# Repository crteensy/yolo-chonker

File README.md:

# yolo-chonker

## if you are a betaflight dev and received an assembled board from crteensy

There is a branch with the "as-built" state that you received: https://github.com/crteensy/yolo-chonker/tree/as-built-20230303

It includes a description of minor mistakes and errors, and what paste (high temp, low temp) was used where.

## What this is

betaflight developer FC for the H735

The layout has 6 layers, and the decoupling is designed for oshpark's 6-layer stackup (see oshpark_6L_stackup.png)

- Format: 30x30 hole distance
- Battery voltage range: 2-6S
- 5V DCDC: LMR33620CRNXT
- 3V3: TPS62824
- Separate DCDC for HD out; LMR33620CRNXT set for 10V or 5V, configured with a solder jumper
- MCU: STM32H735
- peripherals that can be connected to the MCU with solder jumpers:
  - IMU: ICM-20602 and BMI270; dual gyro is possible
  - Flash: S25FL064L
  - Baro: DPS310
  - LEDs:
    - voltage rails LEDs: HD DCDC (5/10 V), 5V, 3V3
    - two standard LEDs for the FC
    - WS2812B including an output pad to attach more
  - battery voltage sensing
- SWD pads
- no analog OSD
- no HD connector

CC-BY-SA-4.0
https://creativecommons.org/licenses/by-sa/4.0/legalcode

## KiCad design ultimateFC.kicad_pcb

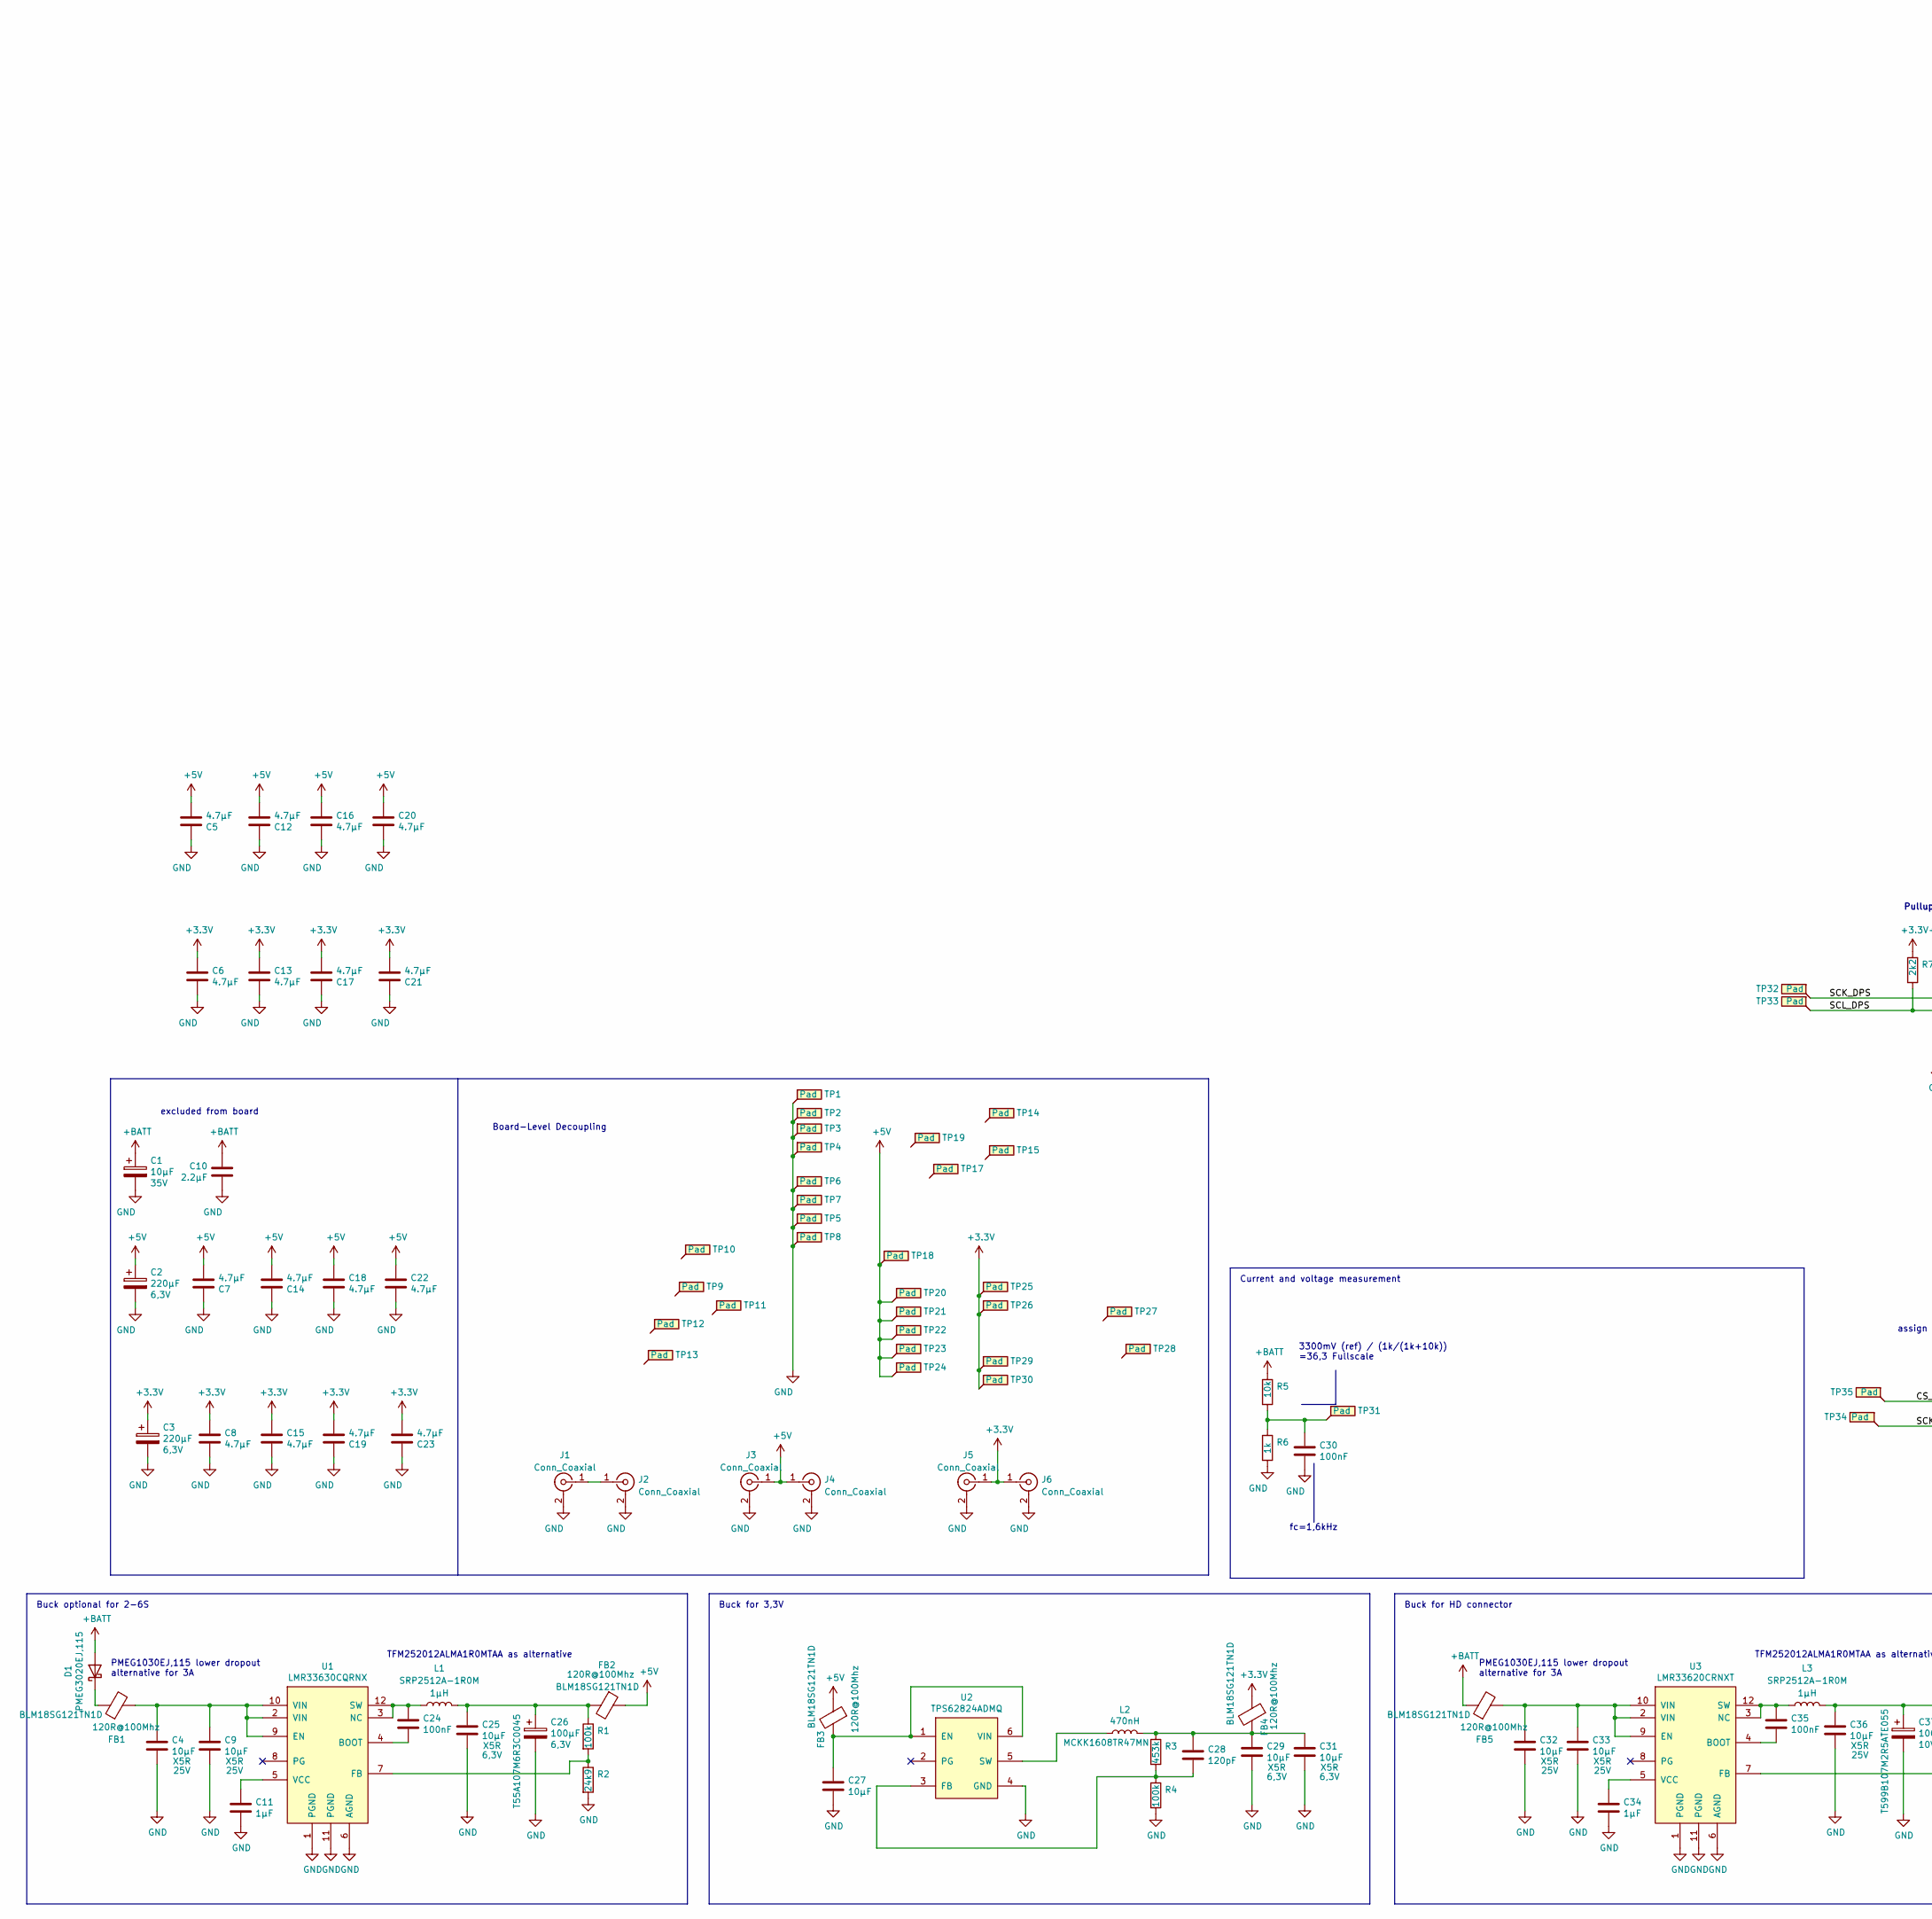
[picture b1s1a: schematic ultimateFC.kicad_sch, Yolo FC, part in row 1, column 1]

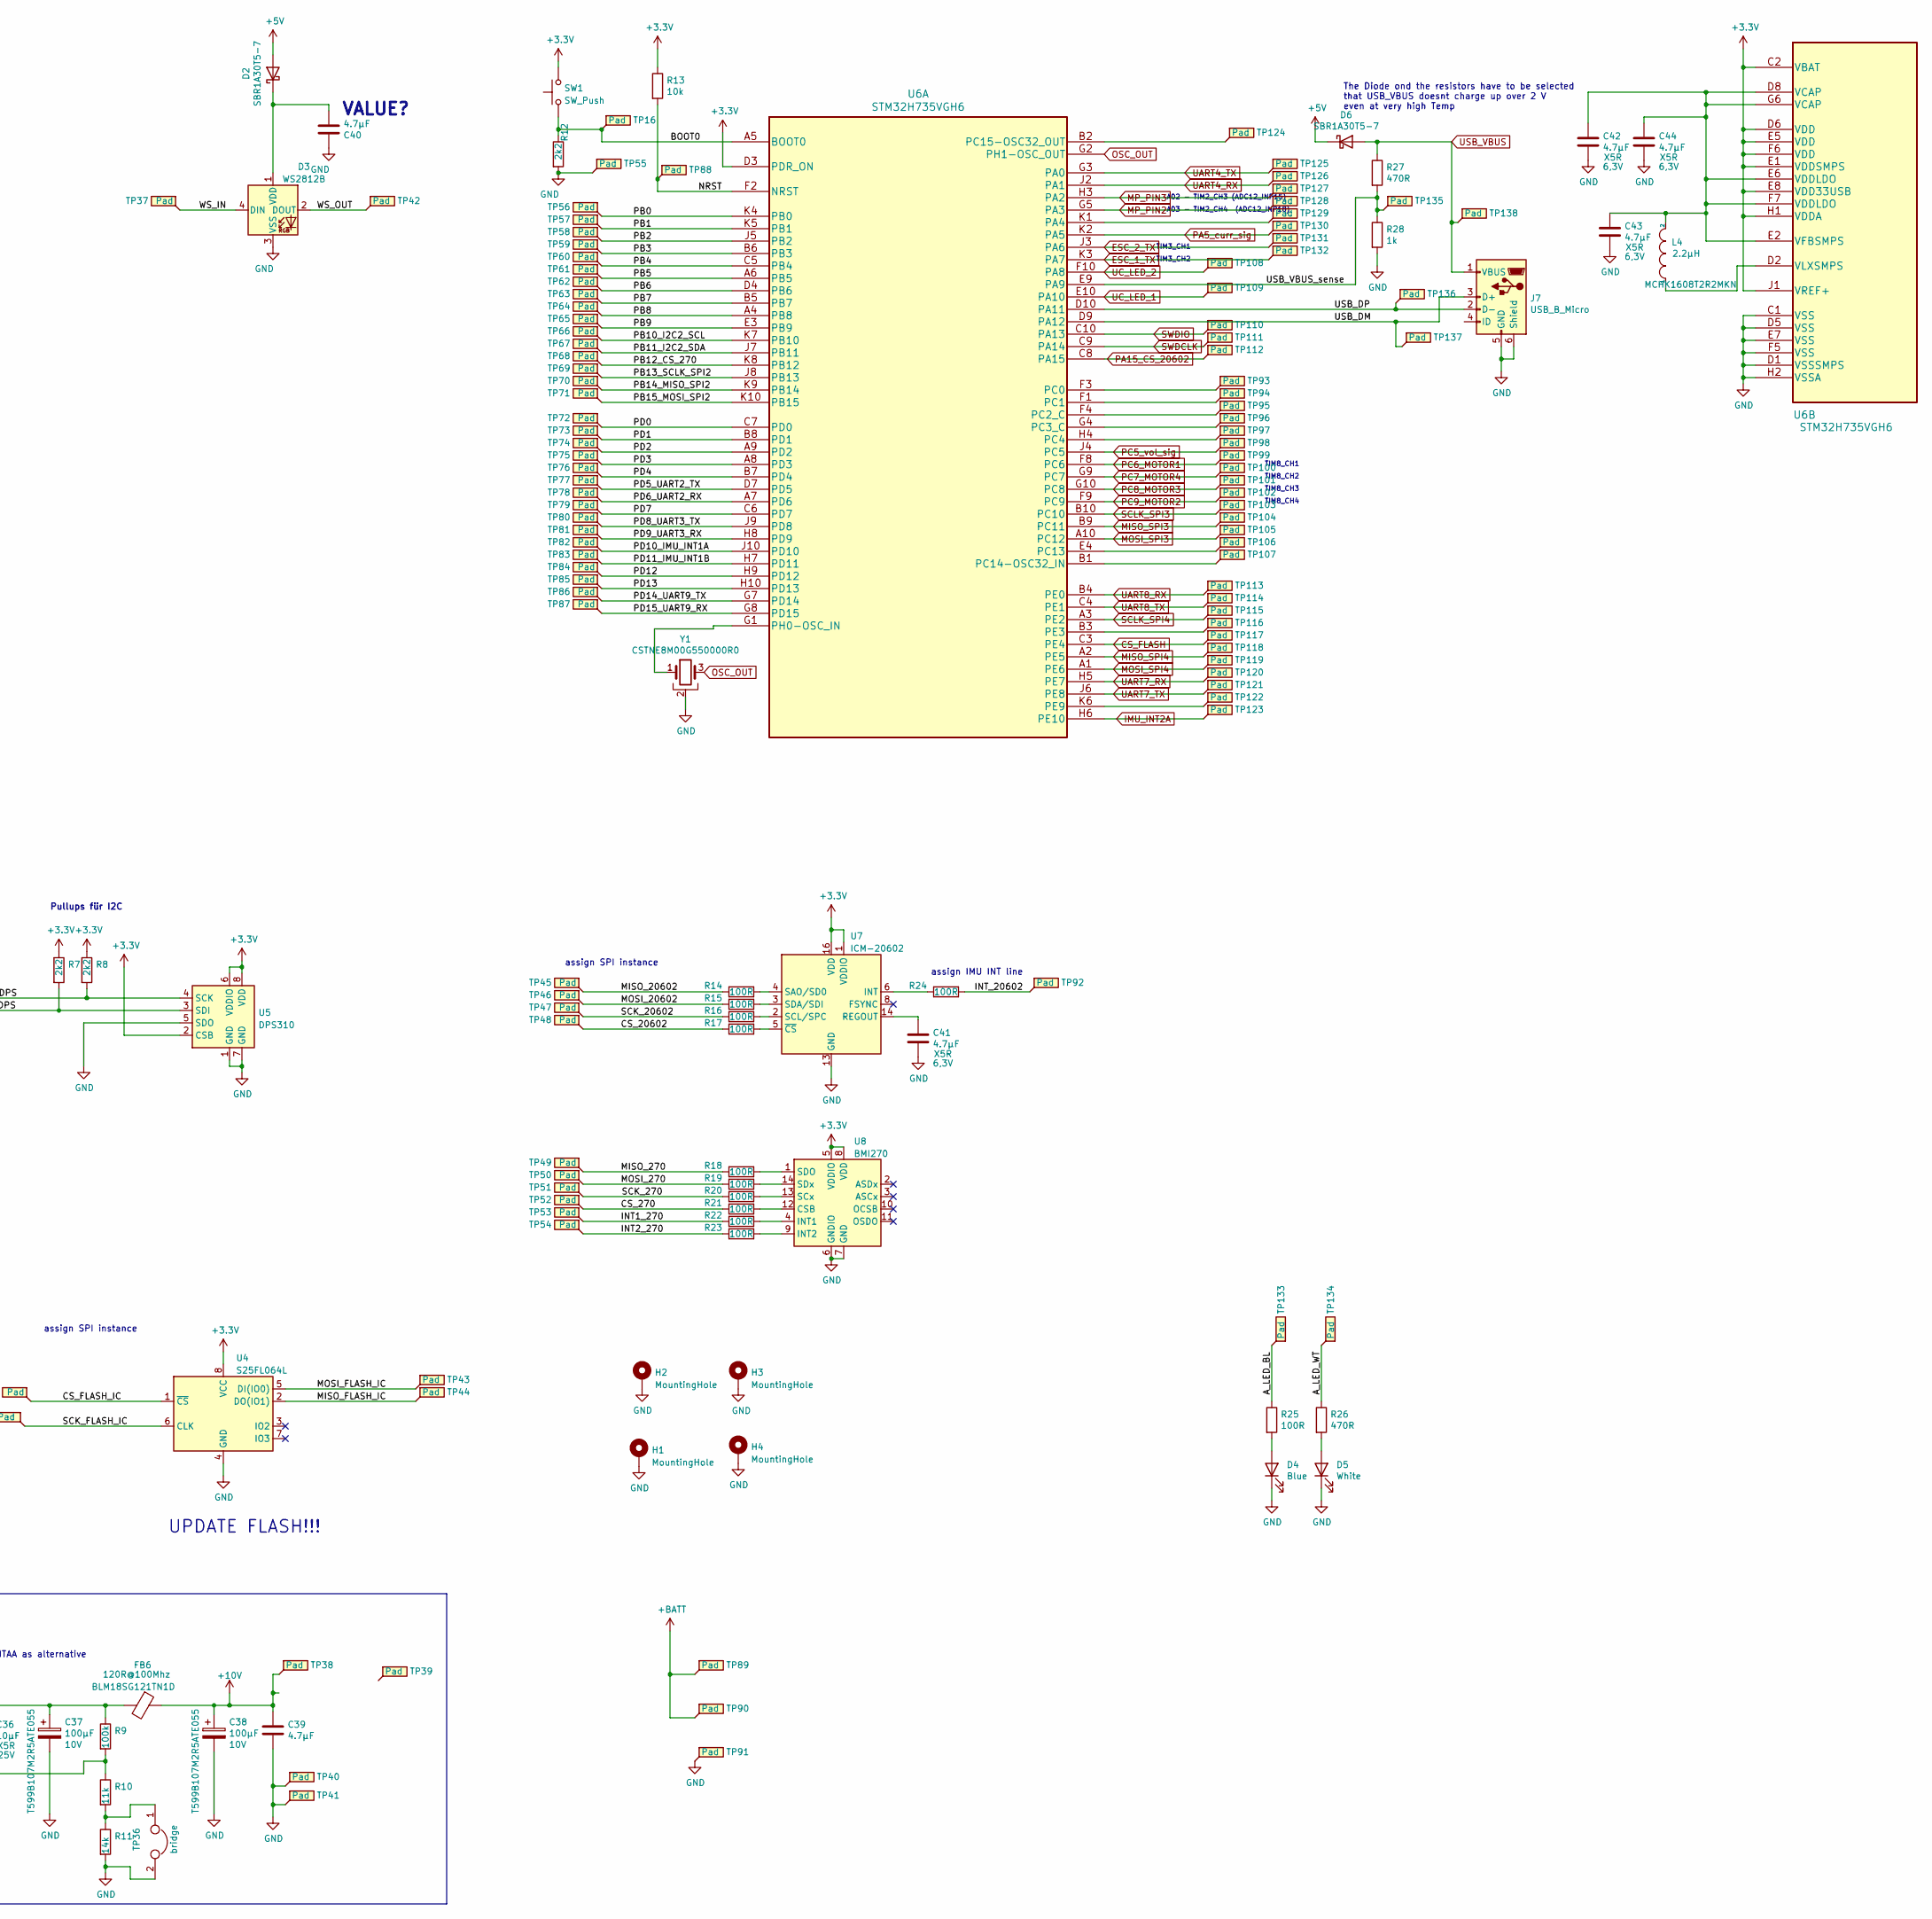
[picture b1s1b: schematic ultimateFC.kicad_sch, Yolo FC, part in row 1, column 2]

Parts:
C1: 10µF; CP_EIA-3216-18_Kemet-A
C2, C3: 220µF; CP_EIA-3528-15_AVX-H
C4, C9, C32, C33, C36: 10µF; C_1206_3216Metric
C5, C6, C7, C8, C12, C13, C14, C15, C16, C17, C18, C19, C20, C21, C22, C23, C39, C41, C42, C43, C44: 4.7µF; C_0402_1005Metric
C10: 2.2µF; C_0603_1608Metric
C11, C34: 1µF; C_0402_1005Metric
C24, C30, C35: 100nF; C_0402_1005Metric
C25, C27, C29, C31: 10µF; C_0603_1608Metric
C26: 100µF; CP_EIA-3216-10_Kemet-I
C28: 120pF; C_0402_1005Metric
C37, C38: 100µF; CP_EIA-3528-12_Kemet-T
C40: 4.7µF; C_0603_1608Metric
D1: PMEG3020EJ,115; D_SOD-323
D2, D6: SBR1A30T5-7; D_SOD-523
D3: WS2812B; LED_WS2812B_PLCC4_5.0x5.0mm_P3.2mm
D4: Blue; LED_0402_1005Metric
D5: White; LED_0402_1005Metric
FB1, FB2, FB3, FB4, FB5, FB6: 120R@100Mhz; L_0603_1608Metric
H1, H2, H3, H4: MountingHole; MountingHole_3.2mm_M3_DIN965_Pad
J1, J2, J3, J4, J5, J6: Conn_Coaxial; Amphenol_RF_A-4JA
J7: USB_B_Micro; USB_Micro-B_Amphenol_10118194_Horizontal
L1, L3: 1µH; L_Wuerth_MAPI-2506
L2: 470nH; L_0603_1608Metric
L4: 2.2µH; L_0603_1608Metric
R1, R4, R9: 100k; R_0402_1005Metric
R2: 24k9; R_0402_1005Metric
R3: 453k; R_0402_1005Metric
R5, R13: 10k; R_0402_1005Metric
R6, R28: 1k; R_0402_1005Metric
R7, R8, R12: 2k2; R_0402_1005Metric
R10: 11k; R_0402_1005Metric
R11: 14k; R_0402_1005Metric
R14, R15, R16, R17, R18, R19, R20, R21, R22, R23, R24, R25: 100R; R_0402_1005Metric
R26, R27: 470R; R_0402_1005Metric
SW1: SW_Push; SW_Push_1P1T-SH_NO_CK_KMR2xxG
TP1, TP3, TP4, TP6, TP7, TP18, TP21, TP22, TP23, TP24, TP29, TP30, TP38, TP40, TP41: Pad; chonker_pwr_pad
TP2, TP5, TP8, TP9, TP10, TP11, TP12, TP13, TP14, TP15, TP16, TP17, TP19, TP20, TP26, TP27, TP28, TP39, TP42, TP56, TP57, TP58, TP59, TP60, TP61, TP62, TP63, TP64, TP65, TP66, TP67, TP68, TP69, TP70, TP71, TP72, TP73, TP74, TP75, TP76, TP77, TP78, TP79, TP80, TP81, TP82, TP83, TP84, TP85, TP86, TP87, TP89, TP93, TP94, TP95, TP96, TP97, TP98, TP99, TP100, TP101, TP102, TP103, TP104, TP105, TP106, TP107, TP108, TP109, TP112, TP113, TP114, TP115, TP116, TP117, TP118, TP119, TP120, TP121, TP122, TP123, TP124, TP125, TP126, TP127, TP128, TP129, TP130, TP131, TP132: Pad; chonker_TestPoint_Pad_1.5x2.0mm
TP25, TP55, TP88, TP110, TP111: Pad; chonker_swd_pad
TP31, TP32, TP33, TP34, TP35, TP37, TP43, TP44, TP45, TP46, TP47, TP48, TP49, TP50, TP51, TP52, TP53, TP54, TP92, TP133, TP134, TP135, TP136, TP137, TP138: Pad; chonker_TestPoint_Pad_1.5x1.5mm
TP36: bridge; solderbridge_tiny
TP90, TP91: Pad; TestPoint_Pad_3.0x3.0mm
U1: LMR33630CQRNX; Texas_RNX0012B
U2: TPS62824ADMQ; VSON_HR6
U3: LMR33620CRNXT; Texas_RNX0012B
U4: S25FL064L; WSON-8_4x4mm_P0.8mm
U5: DPS310; Bosch_LGA-8_2x2.5mm_P0.65mm_ClockwisePinNumbering
U6: STM32H735VGH6; TFBGA-100_8x8mm_Layout10x10_P0.8mm
U7: ICM-20602; LGA-16_3x3mm_P0.5mm_LayoutBorder3x5y
U8: BMI270; Bosch_LGA-14_3x2.5mm_P0.5mm
Y1: CSTNE8M00G550000R0; Resonator_SMD_muRata_CSTxExxV-3Pin_3.0x1.1mm

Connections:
+3V3: C3.1, C6.1, C8.1, C13.1, C15.1, C17.2, C19.2, C21.2, C23.2, FB4.1, J5.1 (In), J6.1 (In), R7.1, R8.1, R13.1, SW1.2, TP25.1, TP26.1, TP29.1, TP30.1, U4.8 (VCC), U5.2 (CSB), U5.6 (VDDIO), U5.8 (VDD), U6.C2 (VBAT), U6.D3 (PDR_ON), U6.D6 (VDD), U6.E1 (VDDSMPS), U6.E5 (VDD), U6.E8 (VDD33USB), U6.F6 (VDD), U6.H1 (VDDA), U6.J1 (VREF+), U7.1 (VDDIO), U7.16 (VDD), U8.5 (VDDIO), U8.8 (VDD)
+5V: C2.1, C5.2, C7.2, C12.2, C14.2, C16.1, C18.1, C20.1, C22.1, D2.2 (A), D6.1 (K), FB2.1, FB3.1, J3.1 (In), J4.1 (In), TP18.1, TP20.1, TP21.1, TP22.1, TP23.1, TP24.1
+10V: C38.1, C39.1, FB6.1, TP38.1
+BATT: C1.1, C10.1, D1.2 (A), FB5.1, R5.1, TP89.1, TP90.1
/A_LED_BL: R25.1, TP133.1
/A_LED_WT: R26.1, TP134.1
/BOOT0: R12.1, SW1.1, TP16.1, U6.A5 (BOOT0)
/CS_270: R21.1, TP52.1
/CS_20602: R17.1, TP48.1
/CS_FLASH_IC: TP35.1, U4.1 (~CS)
/INT1_270: R22.1, TP53.1
/INT2_270: R23.1, TP54.1
/INT_20602: R24.2, TP92.1
/MISO_270: R18.1, TP49.1
/MISO_20602: R14.1, TP45.1
/MISO_FLASH_IC: TP44.1, U4.2 (DO(IO1))
/MOSI_270: R19.1, TP50.1
/MOSI_20602: R15.1, TP46.1
/MOSI_FLASH_IC: TP43.1, U4.5 (DI(IO0))
/NRST: R13.2, TP88.1, U6.F2 (NRST)
/PB0: TP56.1, U6.K4 (PB0)
/PB1: TP57.1, U6.K5 (PB1)
/PB2: TP58.1, U6.J5 (PB2)
/PB3: TP59.1, U6.B6 (PB3)
/PB4: TP60.1, U6.C5 (PB4)
/PB5: TP61.1, U6.A6 (PB5)
/PB6: TP62.1, U6.D4 (PB6)
/PB7: TP63.1, U6.B5 (PB7)
/PB8: TP64.1, U6.A4 (PB8)
/PB9: TP65.1, U6.E3 (PB9)
/PB10_I2C2_SCL: TP66.1, U6.K7 (PB10)
/PB11_I2C2_SDA: TP67.1, U6.J7 (PB11)
/PB12_CS_270: TP68.1, U6.K8 (PB12)
/PB13_SCLK_SPI2: TP69.1, U6.J8 (PB13)
/PB14_MISO_SPI2: TP70.1, U6.K9 (PB14)
/PB15_MOSI_SPI2: TP71.1, U6.K10 (PB15)
/PD0: TP72.1, U6.C7 (PD0)
/PD1: TP73.1, U6.B8 (PD1)
/PD2: TP74.1, U6.A9 (PD2)
/PD3: TP75.1, U6.A8 (PD3)
/PD4: TP76.1, U6.B7 (PD4)
/PD5_UART2_TX: TP77.1, U6.D7 (PD5)
/PD6_UART2_RX: TP78.1, U6.A7 (PD6)
/PD7: TP79.1, U6.C6 (PD7)
/PD8_UART3_TX: TP80.1, U6.J9 (PD8)
/PD9_UART3_RX: TP81.1, U6.H8 (PD9)
/PD10_IMU_INT1A: TP82.1, U6.J10 (PD10)
/PD11_IMU_INT1B: TP83.1, U6.H7 (PD11)
/PD12: TP84.1, U6.H9 (PD12)
/PD13: TP85.1, U6.H10 (PD13)
/PD14_UART9_TX: TP86.1, U6.G7 (PD14)
/PD15_UART9_RX: TP87.1, U6.G8 (PD15)
/SCK_270: R20.1, TP51.1
/SCK_20602: R16.1, TP47.1
/SCK_DPS: R8.2, TP32.1, U5.4 (SCK)
/SCK_FLASH_IC: TP34.1, U4.6 (CLK)
/SCL_DPS: R7.2, TP33.1, U5.3 (SDI)
/USB_DM: J7.3 (D+), TP137.1, U6.D9 (PA12)
/USB_DP: J7.2 (D-), TP136.1, U6.D10 (PA11)
/USB_VBUS_sense: R27.2, R28.1, TP135.1, U6.E9 (PA9)
/WS_IN: D3.4 (DIN), TP37.1
/WS_OUT: D3.2 (DOUT), TP42.1
CS_FLASH: TP117.1, U6.C3 (PE4)
ESC_1_TX: TP132.1, U6.K3 (PA7)
ESC_2_TX: TP131.1, U6.J3 (PA6)
GND: C1.2, C2.2, C3.2, C4.2, C5.1, C6.2, C7.1, C8.2, C9.2, C10.2, C11.2, C12.1, C13.2, C14.1, C15.2, C16.2, C17.1, C18.2, C19.1, C20.2, C21.1, C22.2, C23.1, C25.2, C26.2, C27.2, C29.2, C30.2, C31.2, C32.2, C33.2, C34.2, C36.2, C37.2, C38.2, C39.2, C40.1, C41.2, C42.2, C43.2, C44.2, D3.3 (VSS), D4.1 (K), D5.1 (K), H1.1, H2.1, H3.1, H4.1, J1.2 (Ext), J2.2 (Ext), J3.2 (Ext), J4.2 (Ext), J5.2 (Ext), J6.2 (Ext), J7.5 (GND), J7.6 (Shield), R2.2, R4.2, R6.2, R11.2, R12.2, R28.2, TP1.1, TP2.1, TP3.1, TP4.1, TP5.1, TP6.1, TP7.1, TP8.1, TP36.2, TP40.1, TP41.1, TP55.1, TP91.1, U1.1 (PGND), U1.6 (AGND), U1.11 (PGND), U2.4 (GND), U3.1 (PGND), U3.6 (AGND), U3.11 (PGND), U4.4 (GND), U5.1 (GND), U5.5 (SDO), U5.7 (GND), U6.C1 (VSS), U6.D1 (VSSSMPS), U6.D5 (VSS), U6.E7 (VSS), U6.F5 (VSS), U6.H2 (VSSA), U7.9 (GND), U7.10 (GND), U7.11 (GND), U7.12 (GND), U7.13 (GND), U7.15 (GND), U8.6 (GNDIO), U8.7 (GND), Y1.2
IMU_INT2A: TP123.1, U6.H6 (PE10)
MISO_SPI3: TP104.1, U6.B9 (PC11)
MISO_SPI4: TP118.1, U6.A2 (PE5)
MOSI_SPI3: TP105.1, U6.A10 (PC12)
MOSI_SPI4: TP119.1, U6.A1 (PE6)
MP_PIN2: TP128.1, U6.G5 (PA3)
MP_PIN3: TP127.1, U6.H3 (PA2)
unnamed: C4.1, C9.1, FB1.2, U1.2 (VIN), U1.9 (EN), U1.10 (VIN)
unnamed: C11.1, U1.5 (VCC)
unnamed: C24.1, L1.1, U1.3 (NC), U1.12 (SW)
unnamed: C24.2, U1.4 (BOOT)
unnamed: C25.1, C26.1, FB2.2, L1.2, R1.1
unnamed: C27.1, FB3.2, U2.1 (EN), U2.6 (VIN)
unnamed: C28.1, C29.1, C31.1, FB4.2, L2.2, R3.1
unnamed: C28.2, R3.2, R4.1, U2.3 (FB)
unnamed: C30.1, R5.2, R6.1, TP31.1
unnamed: C32.1, C33.1, FB5.2, U3.2 (VIN), U3.9 (EN), U3.10 (VIN)
unnamed: C34.1, U3.5 (VCC)
unnamed: C35.1, L3.1, U3.3 (NC), U3.12 (SW)
unnamed: C35.2, U3.4 (BOOT)
unnamed: C36.1, C37.1, FB6.2, L3.2, R9.1
unnamed: C40.2, D2.1 (K), D3.1 (VDD)
unnamed: C41.1, U7.14 (REGOUT)
unnamed: C42.1, C43.1, C44.1, L4.2, U6.D8 (VCAP), U6.E2 (VFBSMPS), U6.E6 (VDDLDO), U6.F7 (VDDLDO), U6.G6 (VCAP)
unnamed: D1.1 (K), FB1.1
unnamed: D4.2 (A), R25.2
unnamed: D5.2 (A), R26.2
unnamed: J1.1 (In), J2.1 (In)
unnamed: L2.1, U2.5 (SW)
unnamed: L4.1, U6.D2 (VLXSMPS)
unnamed: R1.2, R2.1, U1.7 (FB)
unnamed: R9.2, R10.1, U3.7 (FB)
unnamed: R10.2, R11.1, TP36.1
unnamed: R14.2, U7.4 (SAO/SD0)
unnamed: R15.2, U7.3 (SDA/SDI)
unnamed: R16.2, U7.2 (SCL/SPC)
unnamed: R17.2, U7.5 (~CS)
unnamed: R18.2, U8.1 (SDO)
unnamed: R19.2, U8.14 (SDx)
unnamed: R20.2, U8.13 (SCx)
unnamed: R21.2, U8.12 (CSB)
unnamed: R22.2, U8.4 (INT1)
unnamed: R23.2, U8.9 (INT2)
unnamed: R24.1, U7.6 (INT)
unnamed: TP93.1, U6.F3 (PC0)
unnamed: TP94.1, U6.F1 (PC1)
unnamed: TP95.1, U6.F4 (PC2_C)
unnamed: TP96.1, U6.G4 (PC3_C)
unnamed: TP97.1, U6.H4 (PC4)
unnamed: TP106.1, U6.E4 (PC13)
unnamed: TP107.1, U6.B1 (PC14-OSC32_IN)
unnamed: TP116.1, U6.B3 (PE3)
unnamed: TP122.1, U6.K6 (PE9)
unnamed: TP124.1, U6.B2 (PC15-OSC32_OUT)
unnamed: TP129.1, U6.K1 (PA4)
unnamed: U6.G1 (PH0-OSC_IN), Y1.1
OSC_OUT: U6.G2 (PH1-OSC_OUT), Y1.3
PA5_curr_sig: TP130.1, U6.K2 (PA5)
PA15_CS_20602: TP112.1, U6.C8 (PA15)
PC5_vol_sig: TP98.1, U6.J4 (PC5)
PC6_MOTOR1: TP99.1, U6.F8 (PC6)
PC7_MOTOR4: TP100.1, U6.G9 (PC7)
PC8_MOTOR3: TP101.1, U6.G10 (PC8)
PC9_MOTOR2: TP102.1, U6.F9 (PC9)
SCLK_SPI3: TP103.1, U6.B10 (PC10)
SCLK_SPI4: TP115.1, U6.A3 (PE2)
SWDCLK: TP111.1, U6.C9 (PA14)
SWDIO: TP110.1, U6.C10 (PA13)
UART4_RX: TP126.1, U6.J2 (PA1)
UART4_TX: TP125.1, U6.G3 (PA0)
UART7_RX: TP120.1, U6.H5 (PE7)
UART7_TX: TP121.1, U6.J6 (PE8)
UART8_RX: TP113.1, U6.B4 (PE0)
UART8_TX: TP114.1, U6.C4 (PE1)
UC_LED_1: TP109.1, U6.E10 (PA10)
UC_LED_2: TP108.1, U6.F10 (PA8)
USB_VBUS: D6.2 (A), J7.1 (VBUS), R27.1, TP138.1

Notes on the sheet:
Board-Level Decoupling
TIM8_CH2
TFM252012ALMA1R0MTAA as alternative
TIM8_CH4
UPDATE FLASH!!!
Buck for 3,3V
A03 - TIM2_CH4 (ADC12_INP18)
TIM8_CH1
TIM8_CH3
TIM3_CH1
excluded from board
assign SPI instance
Buck for HD connector
PMEG1030EJ,115 lower dropout alternative for 3A
3300mV (ref) / (1k/(1k+10k)) =36,3 Fullscale
VALUE?
Current and voltage measurement
assign IMU INT line
Pullups für I2C
TIM3_CH2
fc=1,6kHz
Buck optional for 2-6S
A02 - TIM2_CH3 (ADC12_INP15)
The Diode ond the resistors have to be selected that USB_VBUS doesnt charge up over 2 V even at very high Temp

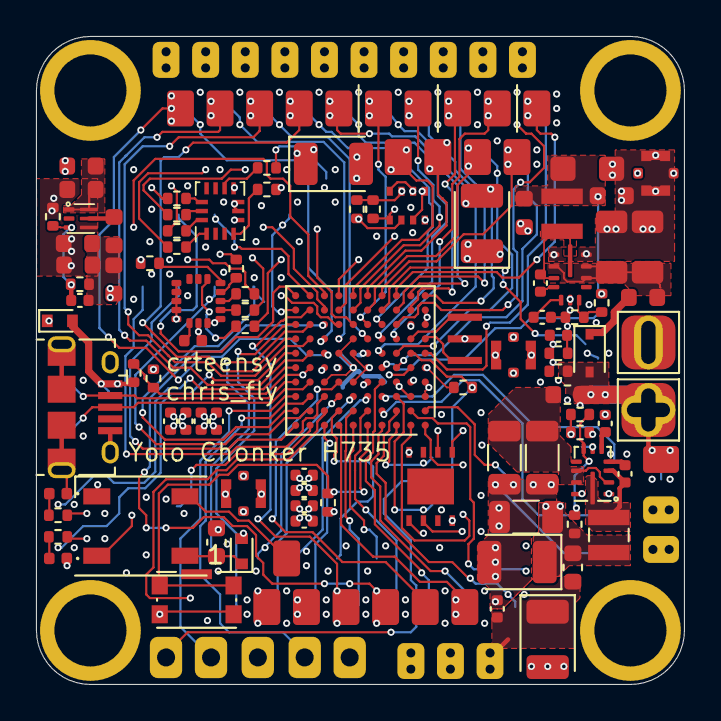
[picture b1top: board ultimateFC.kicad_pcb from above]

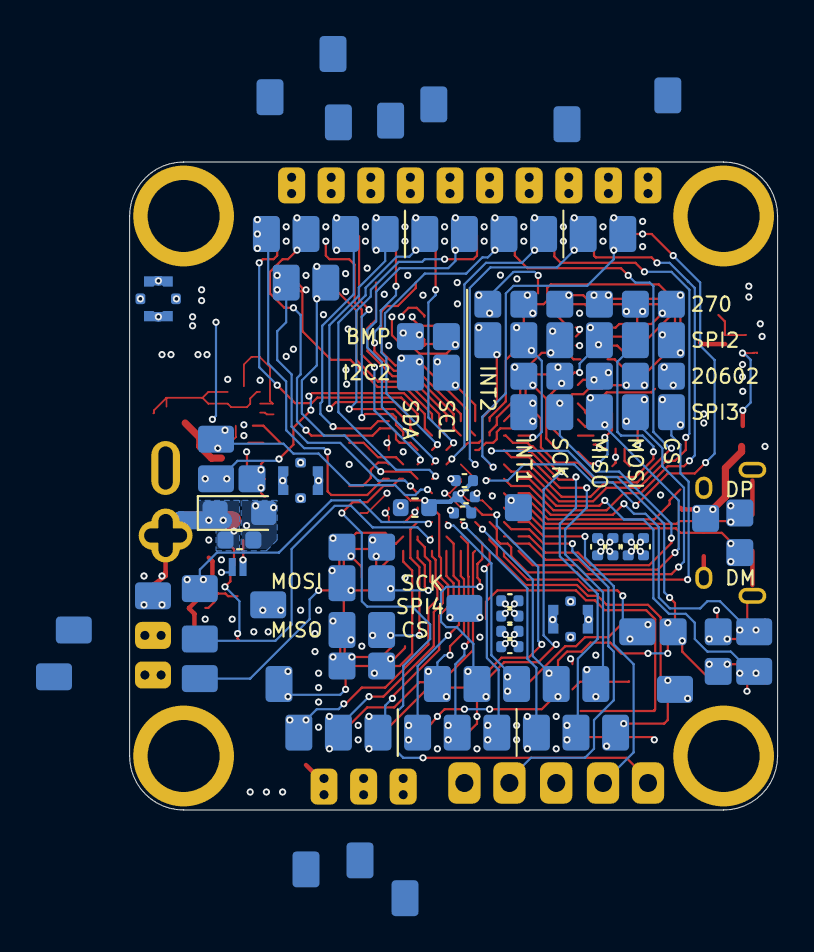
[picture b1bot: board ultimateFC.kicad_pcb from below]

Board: 6 copper layers, 36.0 x 36.0 mm, 247 parts (111 on the bottom side), 143 nets.

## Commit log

2023-01-09 initial schematic and layout
2023-01-09 add HD DCDC
2023-01-09 board edge
2023-01-09 update pcb layer count
2023-01-09 update H7 Power symbol (!)
2023-01-09 added PADs.... lots of PADs
2023-01-10 schematic and layout update
2023-01-11 add DCDC spreadsheet
2023-01-11 more layout
2023-01-11 update layout
2023-01-12 layout update
2023-01-12 add WS2812, update layout
2023-01-13 MORE PADS!!!
2023-01-13 DCDC layouts
2023-01-13 layout tweaks
2023-01-13 add RF connectors
2023-01-13 change pads, add coax datasheet
2023-01-14 Added Caps
2023-01-14 add caps
2023-01-14 tons of vias
2023-01-15 update layout, labels, silkscreen
2023-01-15 Canged to 125u pitch/width & added pad descriptions
2023-01-15 saved schematic
2023-01-15 pad labeling and silkscreen
2023-01-15 last changes before order
2023-03-03 some minor changes
2023-03-03 add assembly pdfs
2023-03-03 add labeling error note in schematic
2023-03-03 schematic: add vis-a-vis pad notes
2023-03-03 add schematic pdf
2023-03-03 update readme, add stackup png
2023-03-03 add top/bot photos
2023-03-03 add license
2023-03-04 add I2C cross jumper photo
2023-03-04 update as-built state schematic annotations low temp layer in layout
2023-03-04 fix errors and mistakes, update schematic
2023-03-25 minor layout tweaks
2023-03-25 minor schematic tweak
2023-04-22 add JLC part numbers
